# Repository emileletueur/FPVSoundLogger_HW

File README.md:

# 🧩 FPVSoundLogger_HW

This the Hardware part of [FPVSoundLogger](https://github.com/SebGalina/FPVSoundLogger)

---

## 📌 General Information

- **EDA Software**: KiCad 9.x  
- **Type**: PCB (number of layers, dimensions)  
- **Status**: In progress / Prototype / Validated  

## 🔐 Licenses

- ⚙️🔓 Hardware: CERN-OHL-S-2.0  
- 💻🔁 Software: GPL-3.0-only  
- 📘✍️ Documentation: CC-BY-4.0

---

## 📂 Project Structure

```
.
├── schematics/     # KiCad schematics
├── pcb/            # PCB layout
├── symbols/        # Custom symbols
├── footprints/     # Custom footprints
├── 3dmodels/       # 3D models (optional / LFS)
├── fabrication/    # Gerbers (git-ignored)
└── README.md
```

---

## ⚡ Key Features

- ✅ Feature 1  
- ✅ Feature 2  
- ✅ Interface X / Power supply Y  

---

## 🔌 Power & Interfaces

| Item          | Specification |
|---------------|---------------|
| Voltage       | 5 V / 12 V    |
| Max current   | xxx mA        |
| Interfaces    | UART / I²C / SPI |

---

## 🧪 Manufacturing

- **PCB**: 2 / 4 layers  
- **Thickness**: 1.6 mm  
- **Copper**: 1 oz  
- **Finish**: HASL / ENIG  
- **Critical tolerances**: yes / no  

> ⚠️ Always use a Git tag for manufacturing releases.

```bash
git tag v1.0-fab
```

---

## 🧾 Version History

| Version | Description            | Date       |
|--------|------------------------|------------|
| v1.0   | Initial prototype      | YYYY-MM-DD |
| v1.1   | Routing fixes          | YYYY-MM-DD |

---

## ✅ Pre‑Manufacturing Checklist

- [ ] ERC with no errors  
- [ ] DRC with no critical violations  
- [ ] Silkscreen readable  
- [ ] Polarities verified  
- [ ] BOM validated  

---

## 👤 Author / Contact

- **Name**:  
- **Email**:  
- **Organization / Project**:

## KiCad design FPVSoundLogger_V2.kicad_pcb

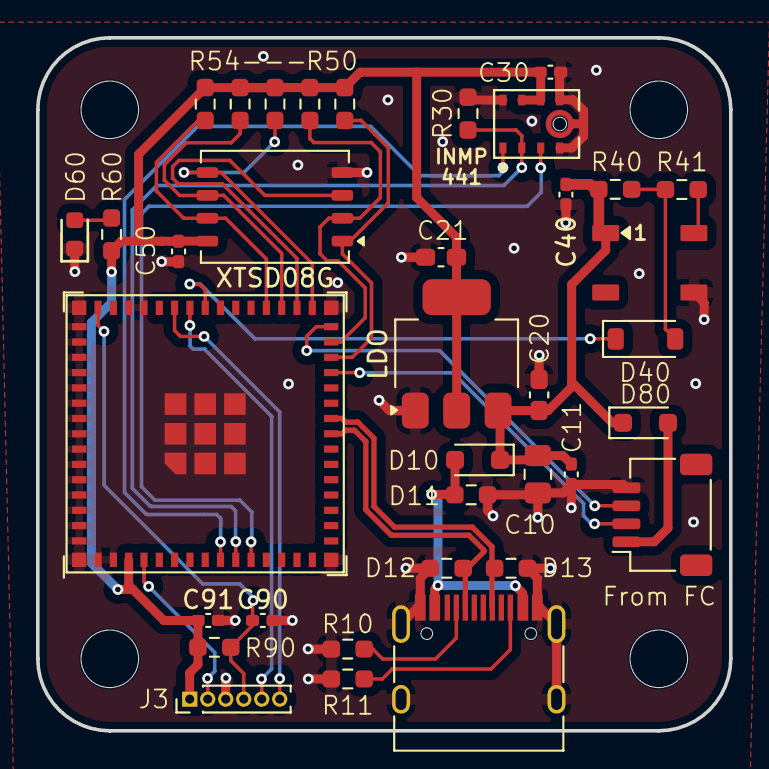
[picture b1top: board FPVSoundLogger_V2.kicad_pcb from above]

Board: 2 copper layers, 38.5 x 38.5 mm, 40 parts (0 on the bottom side), 28 nets.

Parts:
C10: 10uF/16V/X7R; C_0805_2012Metric_Pad1.18x1.45mm_HandSolder
C11: 100nF/16V/X7R; C_0402_1005Metric_Pad0.74x0.62mm_HandSolder
C20: 1uF/16V/X7R; C_0603_1608Metric_Pad1.08x0.95mm_HandSolder
C21: 10uF/16V/X7R; C_0603_1608Metric_Pad1.08x0.95mm_HandSolder
C30, C40, C50, C90, C91: 100nF/10V/X7R; C_0402_1005Metric_Pad0.74x0.62mm_HandSolder
D6: WS2812B; LED_WS2812B_PLCC4_5.0x5.0mm_P3.2mm
D10, D80: B5819; D_SOD-323_HandSoldering
D11, D12, D13: R_0603_1608Metric_Pad0.98x0.95mm_HandSolder
D40: 1N4148W; D_SOD-123
D60: Red; D_0603
From FC: MountingHole; MountingHole_3.2mm_M3
H1, H1#2, H1#3: MountingHole; MountingHole_3.2mm_M3
INMP: INMP441/IVENSENSE-I2S; MIC_INMP441ACEZ-R7
J1: USB_C_Receptacle_USB2.0_16P; USB_C_Receptacle_HRO_TYPE-C-31-M-12
J2: Conn_01x04; JST_SH_SM04B-SRSS-TB_1x04-1MP_P1.00mm_Horizontal
J3: Conn_01x06; PinHeader_1x06_P1.00mm_Vertical
LDO: AMS1117-3.3; SOT-223-3_TabPin2
R10, R11: 5.1kΩ; R_0603_1608Metric_Pad0.98x0.95mm_HandSolder
R30: 100kΩ; R_0603_1608Metric_Pad0.98x0.95mm_HandSolder
R40: 4.7kΩ; R_0603_1608Metric_Pad0.98x0.95mm_HandSolder
R41: 0R; R_0603_1608Metric_Pad0.98x0.95mm_HandSolder
R50: 10kΩ; R_0603_1608Metric_Pad0.98x0.95mm_HandSolder
R51, R52, R53, R54: R_0603_1608Metric_Pad0.98x0.95mm_HandSolder
R60: 1kΩ; R_0603_1608Metric_Pad0.98x0.95mm_HandSolder
R90: 10 kΩ; R_0603_1608Metric_Pad0.98x0.95mm_HandSolder
U1: ESP32-S3-MINI-1U
XTSD08G: XTSD08G; LGA-8_8x6mm_P1.27mm

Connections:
+3V3: C21.1, C30.1, C50.1, C91.1, INMP.7 (VDD), INMP.8 (CHIPEN), J3.1, LDO.2 (VO), R50.1, R51.1, R52.1, R53.1, R54.1, R60.2, R90.1, U1.3 (3V3), XTSD08G.8 (VDD)
+5V: C10.1, C11.1, C20.1, C40.1, D6.1 (VDD), D10.1 (K), D80.1 (K), LDO.3 (VI), R40.2
EN: C90.1, J3.4, R90.2, U1.45 (EN)
ENABLE: J2.2, U1.27 (GPIO47/SPICLK_P/SUBSPICLK_P_DIFF)
GND: C10.2, C11.2, C20.2, C21.2, C30.2, C40.2, C50.2, C90.2, C91.2, D6.3 (VSS), D11.1 (A1), D12.1 (A1), D13.1 (A1), D60.1, INMP.4 (L/R), INMP.5 (GND), INMP.6 (GND), INMP.9 (GND), J1.A1 (GND), J1.A12 (GND), J1.B1 (GND), J1.B12 (GND), J1.S1 (SHIELD), J2.4, J3.3, LDO.1 (GND), R10.1, R11.1, R30.2, U1.1 (GND), U1.2 (GND), U1.42 (GND), U1.43 (GND), U1.46 (GND), U1.47 (GND), U1.48 (GND), U1.49 (GND), U1.50 (GND), U1.51 (GND), U1.52 (GND), U1.53 (GND), U1.54 (GND), U1.55 (GND), U1.56 (GND), U1.57 (GND), U1.58 (GND), U1.59 (GND), U1.60 (GND), U1.61 (GND), U1.62 (GND), U1.63 (GND), U1.64 (GND), U1.65 (GND), XTSD08G.4 (VSS)
GPIO0/BOOT: J3.2, U1.4 (GPIO0/BOOT)
I2S_SCK: INMP.1 (SCK), U1.9 (GPIO5/TOUCH5/ADC1_CH4)
I2S_SD: INMP.2 (SD), R30.1, U1.10 (GPIO6/TOUCH6/ADC1_CH5)
I2S_WS: INMP.3 (WS), U1.11 (GPIO7/TOUCH7/ADC1_CH6)
unnamed: D6.4 (DIN), R41.2
unnamed: D40.2 (A), R40.1, R41.1
unnamed: D60.2, R60.1
unnamed: D80.2 (A), J2.1
unnamed: J1.A5 (CC1), R10.2
unnamed: J1.B5 (CC2), R11.2
RECORD: J2.3, U1.30 (GPIO48/SPICLK_N/SUBSPICLK_N_DIFF)
RGB_CTRL: D40.1 (K), U1.38 (MTMS/GPIO42)
SDIO_CLK: U1.32 (SPIIO7/GPIO36/FSPICLK/SUBSPICLK), XTSD08G.3 (CLK)
SDIO_CMD: R52.2, U1.31 (SPIIO6/GPIO35/FSPID/SUBSPID), XTSD08G.5 (CMD/DI)
SDIO_DATA_0: R53.2, U1.33 (SPIDQS/GPIO37/FSPIQ/SUBSPIQ), XTSD08G.6 (SD0/DO)
SDIO_DATA_1: R54.2, U1.34 (GPIO38/FSPIWP/SUBSPIWP), XTSD08G.7 (SD1)
SDIO_DATA_2: R50.2, U1.28 (SPIIO4/GPIO33/FSPIHD/SUBSPIHD), XTSD08G.1 (SD2)
SDIO_DATA_3: R51.2, U1.29 (SPIIO5/GPIO34/FSPICS0/SUBSPICS0), XTSD08G.2 (SD3/~CS)
U0RXD: J3.6, U1.40 (U0RXD/GPIO44/CLK_OUT2)
U0TXD: J3.5, U1.39 (U0TXD/GPIO43/CLK_OUT1)
USB_D+: D13.2 (A2), J1.A6 (D+), J1.B6 (D+), U1.24 (GPIO20/U1CTS/ADC2_CH9/CLK_OUT1/USB_D+)
USB_D-: D12.2 (A2), J1.A7 (D-), J1.B7 (D-), U1.23 (GPIO19/U1RTS/ADC2_CH8/CLK_OUT2/USB_D-)
VBUS: D10.2 (A), D11.2 (A2), J1.A4 (VBUS), J1.A9 (VBUS), J1.B4 (VBUS), J1.B9 (VBUS)

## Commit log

2026-01-08 fist commit
2026-01-13 v1.0
2026-01-14 update pcb
2026-01-15 version sans err drc
2026-01-15 Ajout .gitignore KiCad
2026-01-15 add readme.md
2026-01-15 add licence files
2026-01-15 remove unsed files
2026-01-15 cleanup
